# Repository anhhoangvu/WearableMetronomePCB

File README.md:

WEARABLE METRONOME by HOANG VU

PCB Repository for the project.

Project for PocketBeagle which uses Python to create an interface for an arm-mounted metronome using vibrational motors to create rhythms and interacting with surrounding sound. Please visit https://www.hackster.io/hoangvu/wearable-metronome-53c2b7 for a complete tutorial and build instructions.

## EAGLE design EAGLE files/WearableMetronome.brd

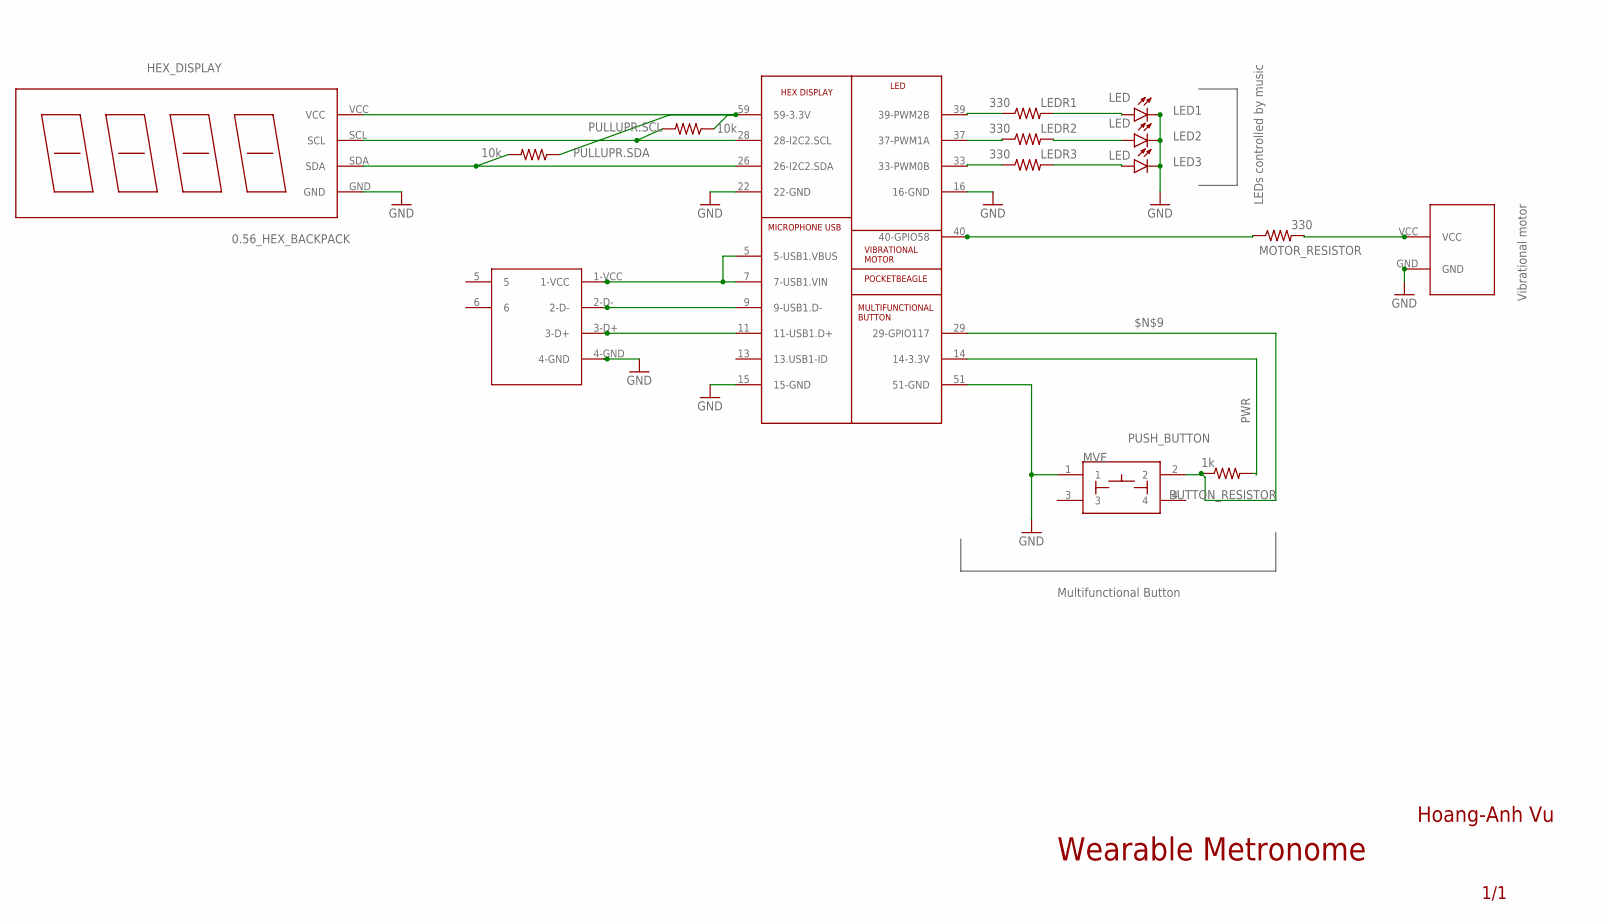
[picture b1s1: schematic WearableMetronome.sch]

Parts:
BUTTON_RESISTOR: 1k; R0603
HEX_DISPLAY: 0.56_HEX_BACKPACK
LED1, LED2, LED3: LED; EIA-STD
LEDR1, LEDR2, LEDR3: 330; R0603
MOTOR_RESISTOR: 330; R0603
MVE: PUSH_BUTTON; BUTTON_12.5MM
PULLUPR.SCL, PULLUPR.SDA: 10k; R0603
U$1: USBAFEMALE
U$2: VIBRATIONALMOTOR
U$3: POCKETBEAGLE_HOANG

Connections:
$N$9: BUTTON_RESISTOR.1, MVE.2, U$3.29 (29-GPIO117)
GND: HEX_DISPLAY.GND, LED1.P$2 (C), LED2.P$2 (C), LED3.P$2 (C), MVE.1, U$1.4-GND, U$2.GND, U$3.15 (15-GND), U$3.16 (16-GND), U$3.22 (22-GND), U$3.51 (51-GND)
unnamed: HEX_DISPLAY.SCL, PULLUPR.SCL.2, U$3.28 (28-I2C2.SCL)
unnamed: HEX_DISPLAY.SDA, PULLUPR.SDA.2, U$3.26 (26-I2C2.SDA)
unnamed: MOTOR_RESISTOR.2, U$2.VCC
unnamed: U$1.1-VCC, U$3.5 (5-USB1.VBUS), U$3.7 (7-USB1.VIN)
unnamed: U$1.2-D-, U$3.9 (9-USB1.D-)
unnamed: U$1.3-D+, U$3.11 (11-USB1.D+)
unnamed: MOTOR_RESISTOR.1, U$3.40 (40-GPIO58)
unnamed: LEDR3.1, U$3.33 (33-PWM0B)
unnamed: LEDR1.1, U$3.39 (39-PWM2B)
unnamed: LED1.P$1 (A), LEDR1.2
unnamed: LEDR2.1, U$3.37 (37-PWM1A)
unnamed: LED2.P$1 (A), LEDR2.2
unnamed: LED3.P$1 (A), LEDR3.2
PWR: BUTTON_RESISTOR.2, HEX_DISPLAY.VCC, PULLUPR.SCL.1, PULLUPR.SDA.1, U$3.14 (14-3.3V), U$3.59 (59-3.3V)

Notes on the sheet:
LEDs controlled by music
Vibrational motor
Multifunctional Button
Wearable Metronome
Hoang-Anh Vu
1/1

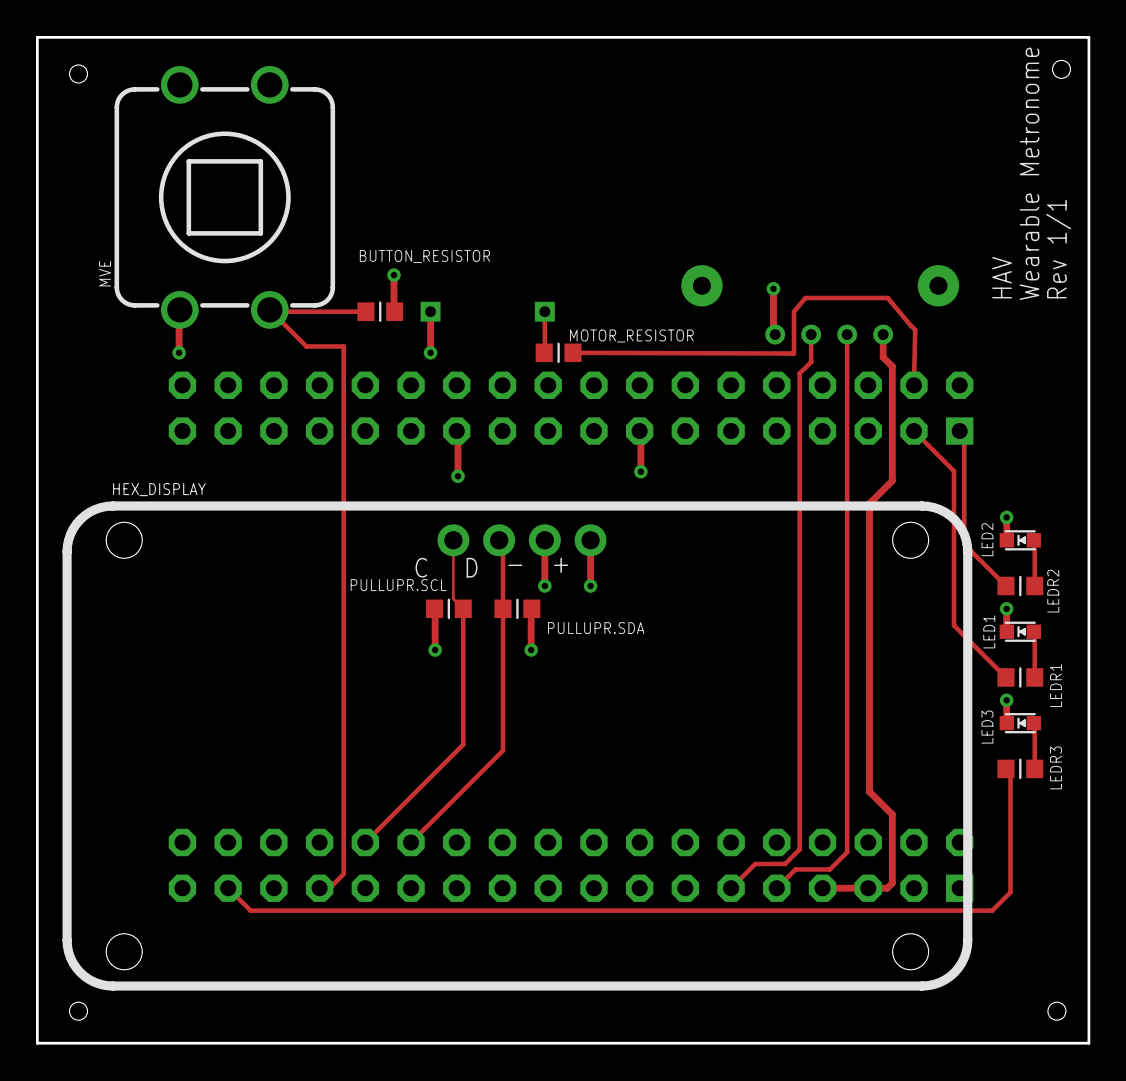
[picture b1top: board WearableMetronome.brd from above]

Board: 2 copper layers, 58.4 x 55.9 mm, 15 parts (1 on the bottom side), 16 nets.

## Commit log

2019-11-27 Create a
2019-12-14 Create d
2019-12-18 Rename EAGLE files/MFG/WearableMetronome.mnt to MFG/WearableMetronome.mnt
2019-12-18 Rename EAGLE files/MFG/WearableMetronome.txt to MFG/WearableMetronome.txt
2019-12-18 Rename EAGLE files/MFG/copper_bottom_l4.gbr to MFG/copper_bottom_l4.gbr
2019-12-18 Rename EAGLE files/MFG/copper_inner_l2.gbr to MFG/copper_inner_l2.gbr
2019-12-18 Rename EAGLE files/MFG/copper_inner_l3.gbr to MFG/copper_inner_l3.gbr
2019-12-18 Rename EAGLE files/MFG/copper_top_l1.gbr to MFG/copper_top_l1.gbr
2019-12-18 Rename EAGLE files/MFG/drills.xln to MFG/drills.xln
2019-12-18 Rename EAGLE files/MFG/gerber_job.gbrjob to MFG/gerber_job.gbrjob
2019-12-18 Rename EAGLE files/MFG/profile.gbr to MGF/profile.gbr
2019-12-18 Rename EAGLE files/MFG/silkscreen_bottom.gbr to MFG/silkscreen_bottom.gbr
2019-12-18 Rename EAGLE files/MFG/silkscreen_top.gbr to MFG/silkscreen_top.gbr
2019-12-18 Rename EAGLE files/MFG/soldermask_bottom.gbr to MFG/soldermask_bottom.gbr
2019-12-18 Rename EAGLE files/MFG/soldermask_top.gbr to MFG/soldermask_top.gbr
2019-12-18 Rename EAGLE files/MFG/solderpaste_bottom.gbr to MFG/solderpaste_bottom.gbr
2019-12-18 Rename EAGLE files/MFG/solderpaste_top.gbr to MFG/solderpaste_top.gbr
2019-12-18 Rename MGF/profile.gbr to MFG/profile.gbr
2019-12-18 Rename WearableMetronome.txt to WearableMetronomeBOM.txt
